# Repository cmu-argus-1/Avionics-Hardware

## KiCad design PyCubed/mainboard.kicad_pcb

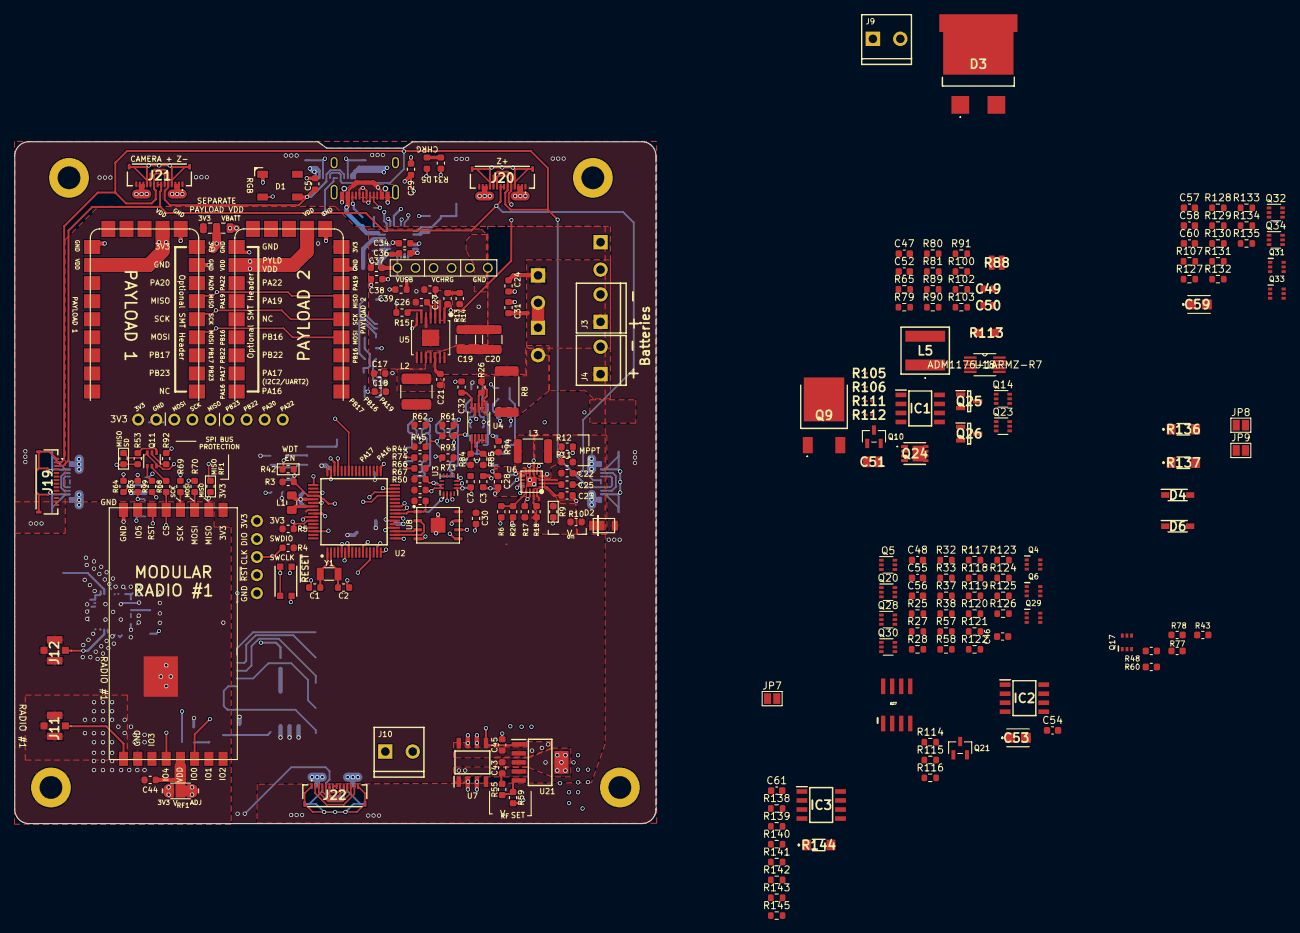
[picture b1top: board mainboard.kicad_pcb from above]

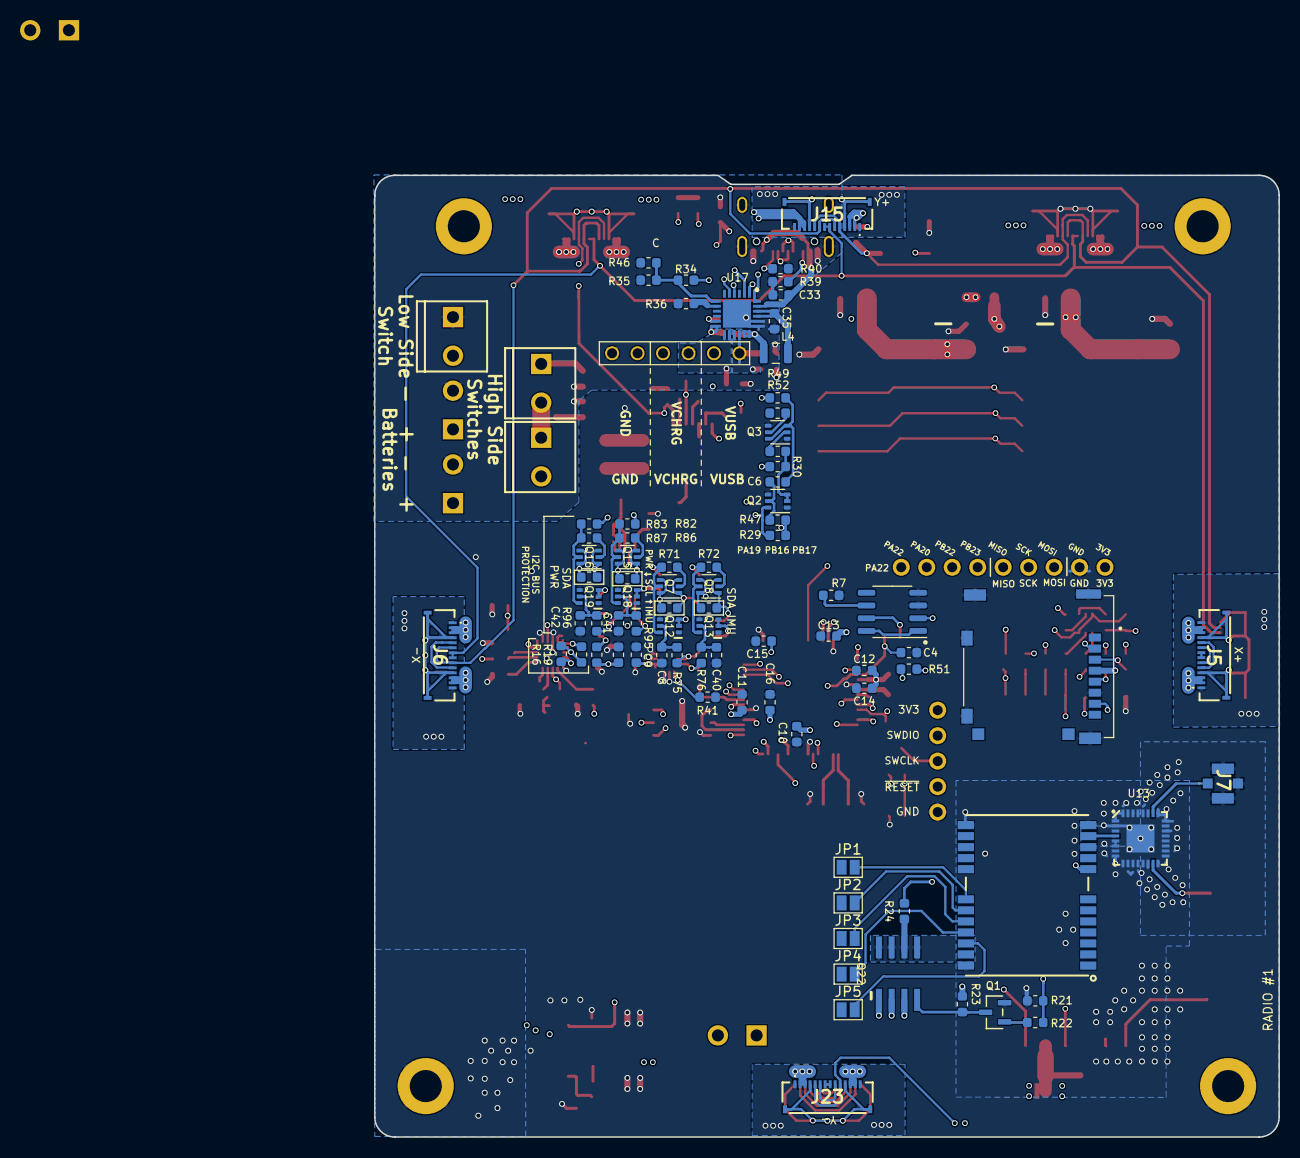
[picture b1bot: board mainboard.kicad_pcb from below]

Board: 4 copper layers, 90.2 x 95.9 mm, 308 parts (85 on the bottom side), 215 nets.

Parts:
C1, C2: 8pF; C_0603_1608Metric
C3, C5, C7, C9, C10, C11, C21, C24, C30, C45, C61: 0.1uF; C_0603_1608Metric
C4, C12, C13, C15, C27, C33, C54, C60: 1uF; C_0603_1608Metric
C6, C14, C16, C22, C35, C39, C43, C44, C52: 10uF; C_0603_1608Metric
C8, C40, C41, C42, C46, C48, C55, C56, C57, C58: 10nF; C_0603_1608Metric
C17, C18, C28, C31, C37, C38: 22uF; C_0603_1608Metric
C19, C20: 100uF; C_1210_3225Metric
C23: 2.2uF; C_0603_1608Metric
C25: 22nF; C_0603_1608Metric
C26, C32, C47: 3.3nF; C_0603_1608Metric
C29, C34: 4.7uF; C_0603_1608Metric
C36: 47nF; C_0603_1608Metric
C49, C50: 0.1u; CAPC1608X87N
C51: 100u; CAPC2012X150N
C53, C59: CPH3225A
D1: WS2812B; LED_WS2812B_PLCC4_5.0x5.0mm_P3.2mm
D2: DFLS130L; PWRDI-123
D3: RB225NS-40TL; RFN10NS3STL
D4, D6: MBR0540T1G; SOD3716X135N
D5: GREEN LED; LED_0603_1608Metric
H1, H2, H3, H4: MountingHole_Pad; MountingHole_3.2mm_M3_DIN965_Pad
IC1: MAX1771ESA+; SOIC127P600X175-8N
IC2: PCF8523T_1,118; SOIC127P600X175-8N
IC3: UA741IDT; SOIC127P600X175-8N
J1: 503182-1852; MOLEX_503182-1852
J2: Conn_01x05; PinHeader_1x05_P2.54mm_Vertical
J3, J4, J9, J10, J16, J17, J18: 1985807; SCREWTERMINAL-3.5MM-2_LOCK
J5, J6, J15, J19, J20, J21, J22, J23: F3311A7H121014E200
J7, J11, J12: 73412-0114; 73412-0110
J8: Conn_01x09; PinHeader_1x09_P2.54mm_Vertical
J13: USB_C_Receptacle_USB2.0; USB_C_Receptacle_XKB_U262-161N-4BVC11
J14: Conn_01x06; PinHeader_1x06_P2.54mm_Vertical
JP1, JP2, JP3, JP4, JP5, JP7, JP8, JP9: SolderJumper_2_Open; SolderJumper-2_P1.3mm_Open_Pad1.0x1.5mm
JP6: Jumper_3_Bridged12; SolderJumper-3_P1.3mm_Bridged12_RoundedPad1.0x1.5mm
L1: 10uH; L_0805_2012Metric_Pad1.15x1.40mm_HandSolder
L2: 3.3uH; L_2141
L3: 33uH; L_1812_4532Metric
L4: 1uH; L_2510
L5: 22u; PA5432223NLT
Q1, Q10, Q21: IRLML2803; SOT-23
Q2, Q3, Q5, Q7, Q8, Q14, Q15, Q16, Q20, Q23, Q28, Q30, Q32, Q34: MBT2222ADW1T1; SOT-363_SC-70-6
Q4, Q6, Q12, Q13, Q17, Q18, Q19, Q29, Q31, Q33: BSS138DWQ-7
Q9: IRFR320TRPBF-BE3; IRFR320TRPBFBE3
Q11: MMDT2907; SOT-363_SC-70-6
Q22, Q27: NDS8434
Q24: SQS141ELNW-T1_GE3; SQS850ENT1_GE3
Q25, Q26: 2SC4713KT146R; SOT95P280X130-3N
R1: 316K; R_0603_1608Metric
R2: 110K; R_0603_1608Metric
R3, R4, R21, R24, R28, R31, R32, R43, R44, R45, R46, R52, R55, R57, R61, R62, R66, R67, R77, R78, R79, R82, R83, R84, R85, R103, R114, R122, R123, R128, R129, R133, R134, R139, R140, R141, R143, R145: 10K; R_0603_1608Metric
R5, R7, R41, R42, R50, R51: 10k; R_0603_1608Metric
R6, R92: 4.7k; R_0603_1608Metric
R8: 0.1; R_2512_6332Metric
R9: 107K; R_0603_1608Metric
R10, R53, R97, R98, R99, R101, R104, R108, R109, R117, R118, R125, R126: 0; R_0603_1608Metric
R11: 787K; R_0603_1608Metric
R12: 121K; R_0603_1608Metric
R13, R29, R89: 73.2K; R_0603_1608Metric
R14: 22.1K; R_0603_1608Metric
R15, R25, R30, R37, R48, R49, R73, R74, R90, R93, R94, R102, R107, R120, R131, R138, R142: 100K; R_0603_1608Metric
R16: 845K; R_0603_1608Metric
R17, R18: 100k; R_0603_1608Metric
R19: 2.1M; R_0603_1608Metric
R20: 3.01K; R_0603_1608Metric
R22, R68, R80, R115: 4.7K; R_0603_1608Metric
R23, R59, R81, R116: 3.3K; R_0603_1608Metric
R26, R63, R64, R65, R69, R70: 1K; R_0603_1608Metric
R27, R38, R60, R71, R72, R86, R87, R121, R127, R132: 680; R_0603_1608Metric
R33, R47, R58, R75, R76, R95, R96, R100, R119, R124, R130, R135: 200K; R_0603_1608Metric
R34: 5.23K; R_0603_1608Metric
R35: 30.1K; R_0603_1608Metric
R36: 3.16K; R_0603_1608Metric
R39, R40: 5.1k; R_0603_1608Metric
R54, R56: 0; R_0805_2012Metric
R88: 20m; ERJB30508
R91, R110: 20K; R_0603_1608Metric
R105, R111: 1k; ERJ1GJJ2R4C
R106: 10k; ERJ1GJJ2R4C
R112: 0; ERJ1GJJ2R4C
R113: 82m; ERJ6_B_BW_R_LW_CW_D
R136, R137: ERA-8VEB1500V; ERA8KEB1004V
R144: ERA-8PEB6803V; ERA8P
SW1: KMR231NG LFS; BTN_KMR2_4.6X2.8
U1: MAX706RESA; SO-8_3.9x4.9mm_P1.27mm
U2: ATSAMD51J19A-AU; QFP50P1200X1200X120-64N
U3: BMX160
U4, U18: ADM1176-1ARMZ-R7
U5: TPS54226PWPRPWP14_2P31X2P46-L; PWP14_2P31X2P46-L
U6: LTC4121; QFN-16-PAD
U7: KF50BD-TR; SOIC127P600X175-8N
U8: MR25H40MDF; SON127P600X500X90-9N
U10, U12: XTB-40; XTB40_payload
U13: EP2W+; QFN32-5X5MM
U14: S1216V8; S1216_24PIN_PACKAGE
U17: BQ25883RGER; QFN50P400X400X100-25N-D
U21: TPS7A4501DCQT
U23: RFM98PW; RFM95PW
Y1: 32.768kHz; Crystal_SMD_3215-2Pin_3.2x1.5mm

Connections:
3.3V: C5.1, C9.2, C10.1, C11.1, C13.1, C15.1, C16.1, C17.2, C18.2, C30.1, D1.1 (VDD), D4.2 (A), D6.2 (A), IC2.8 (VDD), IC3.7 (VCC+), J1.4 (VDD), J2.1, J5.5, J5.10, J6.5, J6.10, J8.1, J15.5, J15.10, J20.5, J20.10, J21.5, J21.10, J23.5, J23.10, JP6.3 (B), L2.2, Q22.1 (Source), Q22.2 (Source), Q22.3 (Source), Q27.1 (Source), Q27.2 (Source), Q27.3 (Source), R3.1, R4.1, R5.1, R13.2, R17.2, R18.2, R23.1, R25.1, R28.1, R32.1, R37.1, R43.1, R44.1, R45.1, R48.1, R50.2, R51.2, R54.1, R57.1, R61.1, R62.1, R66.1, R67.1, R73.1, R74.1, R77.1, R78.1, R82.1, R83.1, R84.1, R85.1, R93.1, R94.1, R107.1, R116.1, R120.1, R122.1, R123.1, R128.1, R129.1, R131.1, R133.1, R134.1, R139.1, R145.2, U1.2 (VCC), U2.4 (PA03), U2.8 (VDDANA), U2.21 (VDDIO), U2.34 (VDDIO1), U2.48 (VDDIO2), U2.56 (VDDIO3), U3.5 (VDDIO), U5.1 (VO), U8.8 (VDD), U10.9, U12.9, U18.9 (A1), U23.9 (3.3V)
/Avionics/BATTERY: C3.1, R1.2, R2.2, U2.15 (PA06)
/Avionics/XTAL1: C1.1, U2.1 (PA00), Y1.1
/Avionics/XTAL2: C2.1, U2.2 (PA01), Y1.2
/Power1/3V3_EN: C49.2, IC1.2 (V+), Q14.6 (C1), Q26.3 (C), R89.2, R106.1
/Power/3V3_EN: Q2.6 (C1), R29.2, U5.7 (EN)
/Power/REGN: C34.1, R31.2, U17.11 (REGN)
/Power/VCHRG_IN: C22.1, D2.C, R10.2, R11.2, U6.P$3 (IN)
/Power/V_RF: C43.2, JP6.1 (A), R55.1, U7.1 (VOUT), U21.4 (OUT)
/RF and GPS/PYLD12_VDD: R54.2, R56.1, U10.11, U10.16, U12.11, U12.16
AIN5: C61.1, IC3.6 (OUTPUT), J8.6, J19.5, R144.2, U2.14 (PA05)
BAT_THERM: J22.2, J22.13, R141.2, R142.2
BURN_RELAY_A: J22.7, J22.8, U2.28 (PB15)
DAC0: J8.8, J19.4, U2.3 (PA02)
ENAB_BURN1: J22.6, J22.9, U2.60 (PB31)
ENAB_BURN2: J22.5, J22.10, U2.32 (PA15)
ENAB_BURN3: J22.4, J22.11, U2.39 (PB16)
ENAB_BURN4: J22.3, J22.12, U2.40 (PB17)
ENAB_GPS: R21.1, R22.1, U2.62 (PB01)
ENAB_IMU: R114.1, R115.1, U2.9 (PB06)
ENAB_JET: R105.1, R111.1
ENAB_RF: U2.13 (PA04), U7.5 (INHIBIT), U21.1 (~SHDN)
FLASH_CS: R50.1, U2.24 (PB11), U8.1 (~CS)
FLASH_IO2: U2.19 (PA10), U8.3 (~WP)
FLASH_IO3: U2.20 (PA11), U8.7 (~HOLD)
FLASH_MISO: U2.18 (PA09), U8.2 (SO)
FLASH_MOSI: U2.17 (PA08), U8.5 (SI)
FLASH_SCK: U2.23 (PB10), U8.6 (SCK)
GND: C1.2, C2.2, C3.2, C4.1, C5.2, C7.2, C8.2, C9.1, C10.2, C11.2, C12.1, C13.2, C14.2, C15.2, C16.2, C17.1, C18.1, C19.2, C20.2, C22.2, C23.2, C26.2, C27.2, C28.2, C30.2, C32.1, C40.2, C41.2, C42.2, C43.1, C44.1, C45.1, C46.2, C47.1, C48.2, C49.1, C50.1, C51.1, C53.2 (-), C54.1, C55.2, C56.2, C57.2, C58.2, C59.2 (-), C60.1, D1.3 (VSS), H1.1, H2.1, H3.1, H4.1, IC1.3 (FB), IC1.6 (AGND), IC1.7 (GND), IC2.4 (VSS), IC3.4 (VCC-), J1.6 (VSS), J1.P1 (SHIELD), J1.P2 (SHIELD), J1.P3 (SHIELD), J1.P4 (SHIELD), J1.P5 (SHIELD), J2.5, J5.4, J5.11, J5.MP1, J5.MP2, J6.4, J6.11, J6.MP1, J6.MP2, J7.2 (GND_1), J7.3 (GND_2), J7.4 (GND_3), J8.2, J9.2, J11.2 (GND_1), J11.3 (GND_2), J11.4 (GND_3), J12.2 (GND_1), J12.3 (GND_2), J12.4 (GND_3), J14.5, J15.4, J15.11, J15.MP1, J15.MP2, J18.2, J19.1, J19.MP1, J19.MP2, J20.4, J20.11, J20.MP1, J20.MP2, J21.4, J21.11, J21.MP1, J21.MP2, J22.1, J22.14, J22.MP1, J22.MP2, J23.4, J23.11, J23.MP1, J23.MP2, Q1.2 (S), Q2.1 (E1), Q2.4 (E2), Q3.1 (E1), Q3.4 (E2), Q4.1 (S2), Q4.4 (S1), Q6.1 (S2), Q6.4 (S1), Q10.2 (S), Q12.1 (S2), Q12.4 (S1), Q13.1 (S2), Q13.4 (S1), Q14.1 (E1), Q14.4 (E2), Q17.1 (S2), Q17.4 (S1), Q18.1 (S2), Q18.4 (S1), Q19.1 (S2), Q19.4 (S1), Q21.2 (S), Q23.1 (E1), Q23.4 (E2), Q25.1 (E), Q29.1 (S2), Q29.4 (S1), Q31.1 (S2), Q31.4 (S1), Q33.1 (S2), Q33.4 (S1), R2.1, R7.1, R9.2, R12.1, R14.1, R20.1, R21.2, R41.2, R59.2, R79.2, R88.1, R112.1, R114.2, R140.2, R143.2, SW1.B (S), SW1.B' (S1), U1.3 (GND), U1.4 (PFI), U2.7 (GND), U2.22 (GND1), U2.33 (GND2), U2.47 (GND3), U2.54 (GND4), U3.2 (GND_1), U3.3 (GND_2), U3.6 (GNDIO), U3.7 (GND_3), U4.4 (GND), U5.5 (GND), U5.8 (PGND1), U5.9 (PGND2), U5.15 (EPAD), U6.P$5 (GND), U6.P$7 (FREQ), U6.P$12 (NTC), U6.P$17 (GND), U7.2 (GND_1), U7.3 (GND_2), U7.6 (GND_3), U7.7 (GND_4), U8.4 (VSS), U8.9 (EP), U10.8, U10.10, U10.15, U12.8, U12.10, U12.15, U13.1 (GND), U13.2 (GND), U13.3 (GND), U13.5 (GND), U13.6 (GND), U13.7 (GND), U13.8 (GND), U13.9 (GND), U13.10 (GND), U13.11 (GND), U13.12 (GND), U13.13 (GND), U13.14 (GND), U13.16 (GND), U13.17 (GND), U13.18 (GND), U13.19 (GND), U13.20 (GND), U13.21 (GND), U13.22 (GND), U13.23 (GND), U13.24 (GND), U13.25 (GND), U13.27 (GND), U13.28 (GND), U13.29 (GND), U13.30 (GND), U13.31 (GND), U13.32 (GND), U13.EP (GND), U14.10 (GND@10), U14.12 (GND@12), U14.13 (GND@13), U14.24 (GND@24), U18.4 (GND), U21.3 (GND_1), U21.6 (GND_2), U23.2 (GND), U23.16 (GND), U23.17 (GND)
GNDREF: C24.2, C29.2, C31.2, C33.1, C34.2, C35.1, C37.1, C38.1, C39.1, J3.2, J4.2, J13.A1 (GND), J13.A12 (GND), J13.S1 (SHIELD), J14.6, J18.1, R35.1, R36.1, R39.1, R40.1, R46.1, U17.19 (GND_1), U17.20 (GND_2), U17.25 (EP)
GPS_PWR_IN: Q22.5 (Drain), Q22.6 (Drain), Q22.7 (Drain), Q22.8 (Drain), R24.2, U14.23 (VCC)
IMU_PWR_IN: C7.1, Q27.5 (Drain), Q27.6 (Drain), Q27.7 (Drain), Q27.8 (Drain), U3.8 (VDD), U3.12 (CSB)
JETSON_PWR: J8.9, J9.1, R65.1, R113.1, U18.2 (SENSE)
JETSON_PWR_SENSE: Q24.5 (D_1), Q24.6 (D_2), Q24.7 (D_3), Q24.8 (D_4), Q24.9 (D_5), Q24.10 (D_6), Q24.11 (D_7), R113.2, U18.1 (VCC)
JETSON_RX: J19.7, U2.37 (PA18)
JETSON_TX: J19.9, U2.35 (PA16)
JETSON_XCK: J19.8, U2.36 (PA17)
L1_PROG: R6.1, R20.2, U6.P$13 (PROG)
MISO: J8.5, Q11.3 (C2), Q11.6 (C1), R101.2, R104.2, U2.31 (PA14), U10.6, U12.6
MISO_RF1: R99.2, R101.1, U23.10 (MISO)
MISO_SD: J1.7 (DAT0), R53.2, R104.1
MOSI: J8.3, R64.2, R70.1, U2.29 (PA12), U10.4, U12.4
MOSI_RF1: R70.2, U23.11 (MOSI)
MOSI_SD: J1.3 (CMD), R64.1
unnamed: C59.1 (+), C60.2, JP5.1 (A)
unnamed: D1.4 (DIN), U2.42 (PA21)
unnamed: D3.3 (A_2), L5.2, Q9.2 (D)
unnamed: D3.4 (K_2), Q24.1 (S_1), Q24.2 (S_2), Q24.3 (S_3), R81.1
unnamed: D4.1 (K), R136.1
unnamed: D5.2 (A), R31.1
unnamed: D6.1 (K), R137.1
unnamed: IC1.8 (CS), Q9.3 (S), R88.2
unnamed: IC1.1 (EXT), Q9.1 (G)
unnamed: C50.2, IC1.5 (REF)
unnamed: IC1.4 (SHDN), Q25.3 (C), R106.2, R112.2
unnamed: C61.2, IC3.2 (INVERTING_INPUT), R142.1, R144.1
unnamed: IC3.3 (NON-INVERTING_INPUT), R138.1, R143.1
unnamed: J7.1 (SIGNAL), U13.26 (PORT2)
unnamed: J12.1 (SIGNAL), U13.15 (PORT1)
unnamed: C37.2, C38.2, J14.1, U17.15 (SYS_1), U17.16 (SYS_2)
unnamed: C39.2, J14.3, U17.13 (BAT_1), U17.14 (BAT_2)
unnamed: J16.2, J17.1
unnamed: JP1.2 (B), U14.18 (SDA/NC)
unnamed: JP2.2 (B), U14.19 (SCL/NC)
unnamed: JP3.2 (B), U14.20 (TXD)
unnamed: JP4.2 (B), U14.21 (RXD)
unnamed: JP5.2 (B), R137.2, U14.22 (V_BCKP)
unnamed: JP7.2 (B), R136.2
unnamed: J19.11, JP8.2 (B)
unnamed: J19.10, JP9.2 (B)
unnamed: Q1.3 (D), Q22.4 (Gate), R23.2
unnamed: Q1.1 (G), R22.2
unnamed: Q2.2 (B1), Q2.3 (C2), R30.2, R110.2
unnamed: C6.2, Q2.5 (B2), R47.2
unnamed: Q3.2 (B1), R110.1
unnamed: C6.1, Q3.3 (C2), Q3.6 (C1), R49.2
unnamed: Q3.5 (B2), R52.1
unnamed: Q4.6 (D1), Q5.5 (B2), R27.2, R28.2
unnamed: Q4.2 (G2), Q4.3 (D2), R25.2
unnamed: C46.1, Q4.5 (G1), R33.2
unnamed: Q5.2 (B1), R27.1
unnamed: Q6.2 (G2), Q6.3 (D2), R37.2
unnamed: C48.1, Q6.5 (G1), R58.2
unnamed: Q7.2 (B1), R71.1
unnamed: Q8.2 (B1), R72.1
unnamed: Q10.3 (D), Q24.4 (G), R81.2
unnamed: Q10.1 (G), R80.2
unnamed: Q11.2 (B1), R68.1
unnamed: Q11.1 (E1), R99.1
unnamed: Q11.5 (B2), R92.1
unnamed: Q11.4 (E2), R53.1
unnamed: Q7.5 (B2), Q12.6 (D1), R61.2, R71.2
unnamed: Q12.2 (G2), Q12.3 (D2), R73.2
unnamed: C8.1, Q12.5 (G1), R75.2
unnamed: Q8.5 (B2), Q13.6 (D1), R62.2, R72.2
unnamed: Q13.2 (G2), Q13.3 (D2), R74.2
unnamed: C40.1, Q13.5 (G1), R76.2
unnamed: Q14.2 (B1), Q14.3 (C2), R90.2, R91.2
unnamed: C52.2, Q14.5 (B2), R100.2
unnamed: Q15.2 (B1), R86.1
unnamed: Q15.5 (B2), Q18.6 (D1), R82.2, R86.2
unnamed: Q16.2 (B1), R87.1
unnamed: Q16.5 (B2), Q19.6 (D1), R83.2, R87.2
unnamed: Q17.6 (D1), Q28.5 (B2), R60.2, R77.2
unnamed: Q17.2 (G2), Q17.3 (D2), R48.2
unnamed: C55.1, Q17.5 (G1), R119.2
unnamed: Q18.2 (G2), Q18.3 (D2), R93.2
unnamed: C41.1, Q18.5 (G1), R95.2
unnamed: Q19.2 (G2), Q19.3 (D2), R94.2
unnamed: C42.1, Q19.5 (G1), R96.2
unnamed: Q20.2 (B1), R38.1
unnamed: Q6.6 (D1), Q20.5 (B2), R38.2, R43.2
unnamed: Q21.3 (D), Q27.4 (Gate), R116.2
unnamed: Q21.1 (G), R115.2
unnamed: Q23.2 (B1), R91.1
unnamed: C52.1, Q23.3 (C2), Q23.6 (C1), R102.2
unnamed: Q23.5 (B2), R103.1
unnamed: Q25.2 (B), R105.2
unnamed: Q26.2 (B), R111.2
unnamed: C51.2, Q26.1 (E), R79.1, R80.1
unnamed: Q28.2 (B1), R60.1
unnamed: Q29.6 (D1), Q30.5 (B2), R121.2, R122.2
unnamed: Q29.2 (G2), Q29.3 (D2), R120.2
unnamed: C56.1, Q29.5 (G1), R124.2
unnamed: Q30.2 (B1), R121.1
unnamed: Q31.6 (D1), Q32.5 (B2), R127.2, R128.2
unnamed: Q31.2 (G2), Q31.3 (D2), R107.2
unnamed: C57.1, Q31.5 (G1), R130.2
unnamed: Q32.2 (B1), R127.1
unnamed: Q33.6 (D1), Q34.5 (B2), R132.2, R133.2
unnamed: Q33.2 (G2), Q33.3 (D2), R131.2
unnamed: C58.1, Q33.5 (G1), R135.2
unnamed: Q34.2 (B1), R132.1
unnamed: R138.2, R139.2, R140.1
unnamed: R141.1, R145.1
unnamed: U1.1 (~MR), U1.8 (~WDO)
unnamed: R42.2, U1.7 (~RESET)
unnamed: R6.2, U2.16 (PA07)
unnamed: C12.2, C14.1, L1.1, U2.53 (VDDCORE)
unnamed: L1.2, U2.55 (VSW)
unnamed: R41.1, U3.1 (SDO)
unnamed: R26.2, U4.3 (ON)
unnamed: C32.2, U4.5 (TIMER)
unnamed: R15.1, U5.6 (PG)
unnamed: C26.1, U5.4 (SS)
unnamed: C21.1, L2.1, U5.10 (SW1), U5.11 (SW2)
unnamed: C21.2, U5.12 (VBST)
unnamed: R13.1, R14.2, U5.2 (VFB)
unnamed: C27.1, R15.2, U5.3 (VREG5)
unnamed: C25.1, U6.P$2 (BOOST)
unnamed: L3.1, U6.P$8 (CHGSNS)
unnamed: R16.2, R19.2, U6.P$10 (FB)
unnamed: R16.1, U6.P$11 (FBG)
unnamed: C23.1, U6.P$1 (INTVCC)
unnamed: R11.1, R12.2, U6.P$6 (MPPT)
unnamed: R9.1, R10.1, U6.P$16 (RUN)
unnamed: C25.2, L3.2, U6.P$4 (SW)
unnamed: R18.1, U6.P$15 (~FAULT)
unnamed: U13.4 (SUM_PORT), U14.11 (RF_IN)
unnamed: R24.1, U14.8 (RSTN)
unnamed: C36.2, U17.12 (BTST)
unnamed: R36.2, U17.8 (ILIM)
unnamed: C35.2, L4.1, U17.21 (PMID_1), U17.22 (PMID_2)
unnamed: C36.1, L4.2, U17.17 (SW_1), U17.18 (SW_2)
unnamed: R65.2, U18.3 (ON)
unnamed: C47.2, U18.5 (TIMER)
unnamed: R55.2, R59.1, U21.5 (SENSE/ADJ)
PB07: J19.12, U2.10 (PB07)
PB09: J19.13, U2.12 (PB09)
PB14: J19.14, U2.27 (PB14)
PB22: J8.7, J19.6, U2.49 (PB22)
RF1_ANT: J11.1 (SIGNAL), U23.1 (ANT)
RF1_CS: R5.2, R68.2, U2.59 (PB30), U23.13 (NSS)
RF1_IO0: U2.6 (PB05), U23.6 (GPIO_0)
RF1_IO4: U2.5 (PB04), U23.4 (GPIO_4)
RF1_RST: U2.61 (PB00), U23.14 (RESET)
RX: JP3.1 (A), JP8.1 (A), U2.64 (PB03)
SCK: J8.4, R63.2, R69.2, U2.30 (PA13), U10.5, U12.5
SCK_RF1: R69.1, U23.12 (SCK)
SCK_SD: J1.5 (CLK), R63.1
SCL: Q5.1 (E1), Q5.3 (C2), Q7.1 (E1), Q7.3 (C2), Q15.1 (E1), Q15.3 (C2), Q28.1 (E1), Q28.3 (C2), Q32.1 (E1), Q32.3 (C2), R45.2, R97.2, R108.2, R117.2, R125.2, U2.26 (PB13)
SCL2: J5.6, J5.9, J6.6, J6.9, J15.6, J15.9, J19.2, J20.6, J20.9, J21.6, J21.9, J23.6, J23.9, U2.44 (PA23)
SCL_GPS: JP2.1 (A), Q32.4 (E2), Q32.6 (C1), R129.2, R130.1
SCL_IMU: Q7.4 (E2), Q7.6 (C1), R66.2, R75.1, R97.1, U3.13 (SCX)
SCL_JETSON_PWR: Q28.4 (E2), Q28.6 (C1), R78.2, R119.1, R125.1, U18.6 (SCL)
SCL_PWR: Q15.4 (E2), Q15.6 (C1), R84.2, R95.1, R108.1, U4.6 (SCL), U17.5 (SCL)
SCL_RTC: IC2.6 (SCL), Q5.4 (E2), Q5.6 (C1), R32.2, R33.1, R117.1
SDA: Q8.1 (E1), Q8.3 (C2), Q16.1 (E1), Q16.3 (C2), Q20.1 (E1), Q20.3 (C2), Q30.1 (E1), Q30.3 (C2), Q34.1 (E1), Q34.3 (C2), R44.2, R98.2, R109.2, R118.2, R126.2, U2.25 (PB12)
SDA2: J5.7, J5.8, J6.7, J6.8, J15.7, J15.8, J19.3, J20.7, J20.8, J21.7, J21.8, J23.7, J23.8, U2.43 (PA22)
SDA_GPS: JP1.1 (A), Q34.4 (E2), Q34.6 (C1), R134.2, R135.1
SDA_IMU: Q8.4 (E2), Q8.6 (C1), R67.2, R76.1, R98.1, U3.14 (SDX)
SDA_JETSON_PWR: Q30.4 (E2), Q30.6 (C1), R123.2, R124.1, R126.1, U18.7 (SDA)
SDA_PWR: Q16.4 (E2), Q16.6 (C1), R85.2, R96.1, R109.1, U4.7 (SDA), U17.4 (SDA)
SDA_RTC: IC2.5 (SDA), Q20.4 (E2), Q20.6 (C1), R57.2, R58.1, R118.1
SD_CS: J1.2 (CD/DAT3), R51.1, R92.2, U2.51 (PA27)
STAT: D5.1 (K), U17.2 (STAT)
SWCLK: J2.3, R4.2, U2.57 (PA30)
SWDIO: J2.2, U2.58 (PA31)
THM: R34.2, R35.2, R46.2, U17.7 (TS)
TX: JP4.1 (A), JP9.1 (A), U2.63 (PB02)
USB_CC1: J13.A5 (CC1), R40.2
USB_CC2: J13.B5 (CC2), R39.2
USB_D+: J13.A6 (D+), J13.B6 (D+), U2.46 (PA25), U17.24 (D+)
USB_D-: J13.A7 (D-), J13.B7 (D-), U2.45 (PA24), U17.1 (D-)
VBATT: C19.1, C20.1, C28.1, C45.2, J5.2, J5.3, J5.12, J5.13, J6.2, J6.3, J6.12, J6.13, J10.1, J10.2, J14.2, J15.2, J15.3, J15.12, J15.13, J20.2, J20.3, J20.12, J20.13, J21.2, J21.3, J21.12, J21.13, J23.2, J23.3, J23.12, J23.13, L5.1, R1.1, R8.1, R19.1, R26.1, R29.1, R30.1, R47.1, R49.1, R56.2, R89.1, R90.1, R100.1, R102.1, U4.2 (SENSE), U5.13 (VIN), U5.14 (VCC), U6.P$9 (BAT), U7.8 (VIN), U21.2 (IN)
VBATT_SENSE: J17.2, R8.2, U4.1 (VCC)
VBUS_IN: C29.1, C33.2, J13.A4 (VBUS), J13.A9 (VBUS), R34.1, U17.23 (VBUS)
VBUS_RESET: R52.2, R103.2, U2.41 (PA20)
VCC_RF1: C44.2, JP6.2 (C), U23.5 (VCC)
VCELL: C53.1 (+), C54.2, IC2.3 (VBAT), JP7.1 (A)
VCHRG: C24.1, C31.1, J3.1, J4.1, J14.4, J16.1
VSOLAR: D2.A, J5.1, J5.14, J6.1, J6.14, J15.1, J15.14, J20.1, J20.14, J21.1, J21.14, J23.1, J23.14
WDT_WDI: R7.2, U1.6 (~WDI), U2.50 (PB23)
~CHRG: R17.1, U2.11 (PB08), U6.P$14 (~CHRG)
~RESET: C4.2, J2.4, R3.2, R42.1, SW1.A, SW1.A' (P1), U2.52 (RESETN)

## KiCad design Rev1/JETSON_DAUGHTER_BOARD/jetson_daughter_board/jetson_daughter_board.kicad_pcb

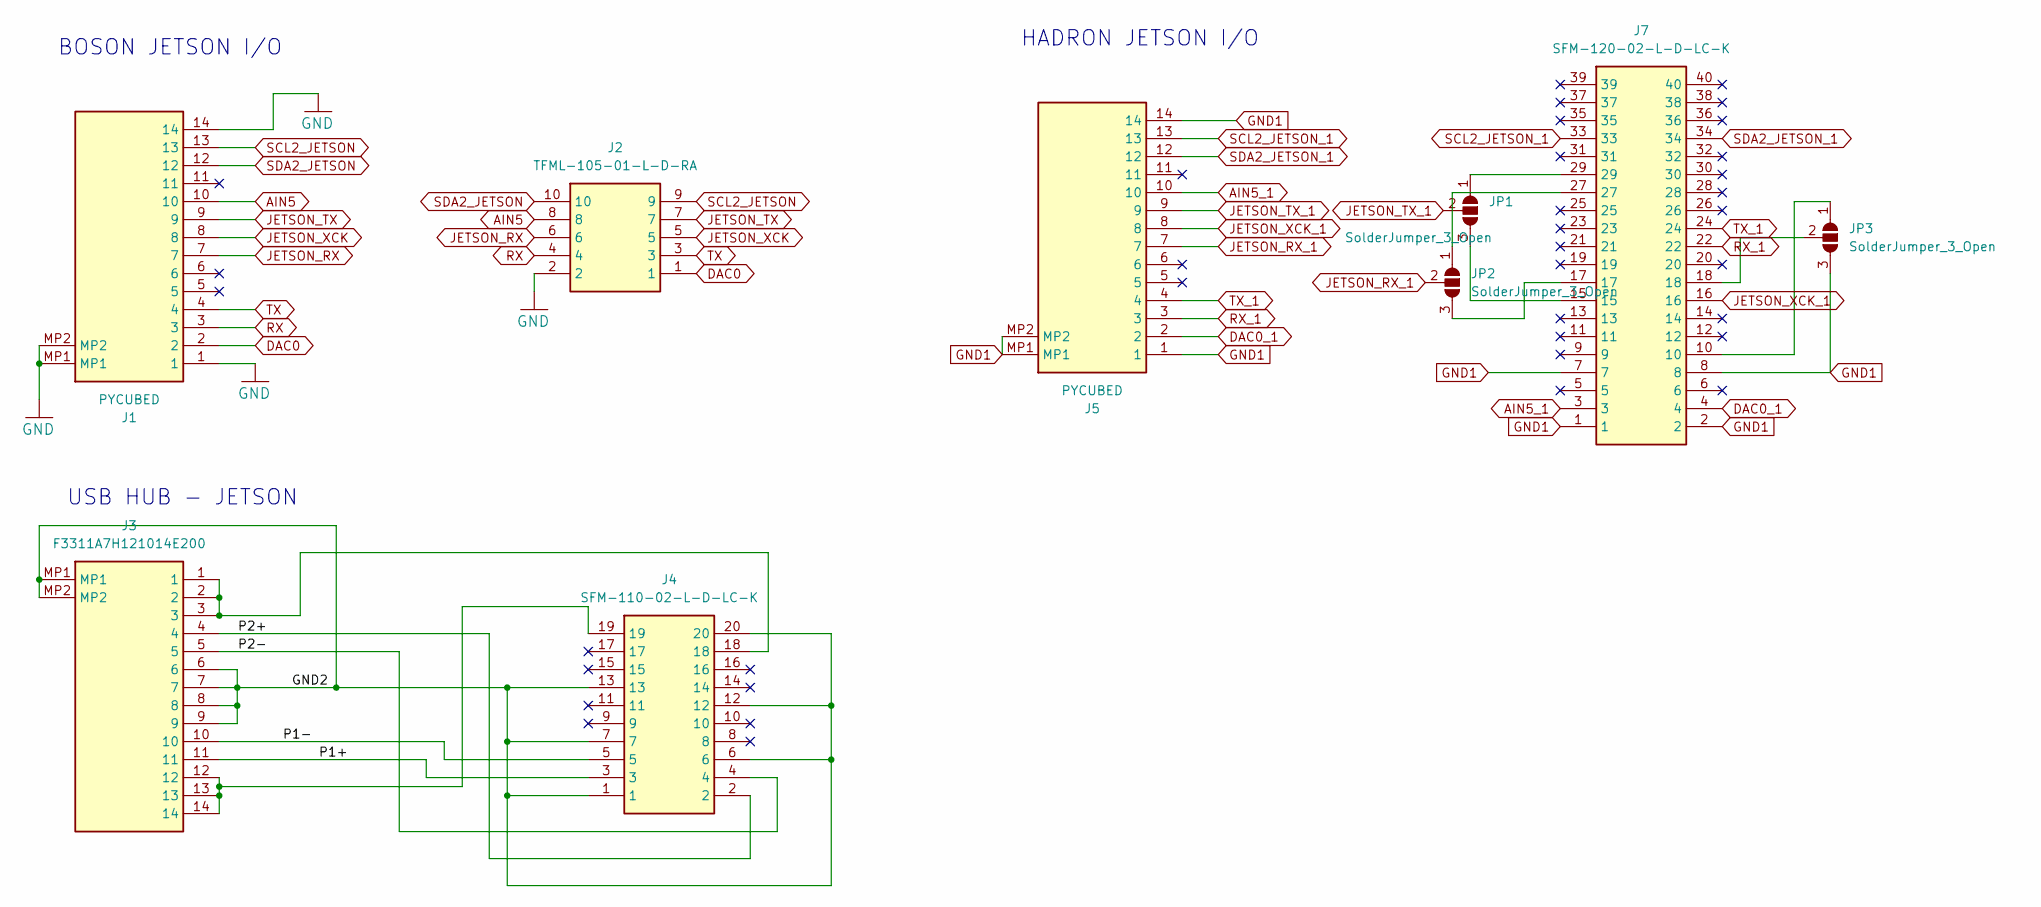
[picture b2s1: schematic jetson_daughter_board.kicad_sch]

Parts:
J1, J5: PYCUBED; F3311A7H121014E200; Manufacturer_Part_Number F3311A7H121014E200
J2: TFML-105-01-L-D-RA; TFML10501LDRA; Manufacturer_Part_Number TFML-105-01-L-D-RA; Mouser Part Number 200-TFML10501LDRA
J3: F3311A7H121014E200; Manufacturer_Part_Number F3311A7H121014E200
J4: SFM-110-02-L-D-LC-K; SFM11002LDLCK; Manufacturer_Part_Number SFM-110-02-L-D-LC-K; Mouser Part Number 200-SFM11002LDLCK
J7: SFM-120-02-L-D-LC-K; SFM12002LDLCK; Manufacturer_Part_Number SFM-120-02-L-D-LC-K; Mouser Part Number 200-SFM12002LDLCK
JP1, JP2, JP3: SolderJumper_3_Open; SolderJumper-3_P1.3mm_Open_Pad1.0x1.5mm

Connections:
/P1+: J3.11, J4.3
/P1-: J3.10, J4.5
/P2+: J3.4, J4.2
/P2-: J3.5, J4.4
AIN5: J1.10, J2.8
AIN5_1: J5.10, J7.3
DAC0: J1.2, J2.1
DAC0_1: J5.2, J7.4
GND: J1.1, J1.14, J1.MP1, J1.MP2, J2.2
GND1: J5.1, J5.14, J5.MP1, J5.MP2, J7.1, J7.2, J7.7, J7.8, JP3.3 (B)
GND2: J3.6, J3.7, J3.8, J3.9, J3.MP1, J3.MP2, J4.1, J4.6, J4.7, J4.12, J4.13, J4.20
JETSON_RX: J1.7, J2.6
JETSON_RX_1: J5.7, JP2.2 (C)
JETSON_TX: J1.9, J2.7
JETSON_TX_1: J5.9, JP1.2 (C)
JETSON_XCK: J1.8, J2.5
JETSON_XCK_1: J5.8, J7.16
unnamed: J3.1, J3.2, J3.3, J4.18
unnamed: J3.12, J3.13, J3.14, J4.19
unnamed: J7.29, JP1.1 (A)
unnamed: J7.15, JP1.3 (B)
unnamed: J7.27, JP2.1 (A)
unnamed: J7.17, JP2.3 (B)
unnamed: J7.10, JP3.1 (A)
unnamed: J7.18, JP3.2 (C)
RX: J1.3, J2.4
RX_1: J5.3, J7.22
SCL2_JETSON: J1.13, J2.9
SCL2_JETSON_1: J5.13, J7.33
SDA2_JETSON: J1.12, J2.10
SDA2_JETSON_1: J5.12, J7.34
TX: J1.4, J2.3
TX_1: J5.4, J7.24

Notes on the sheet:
USB HUB - JETSON
BOSON JETSON I/O
HADRON JETSON I/O

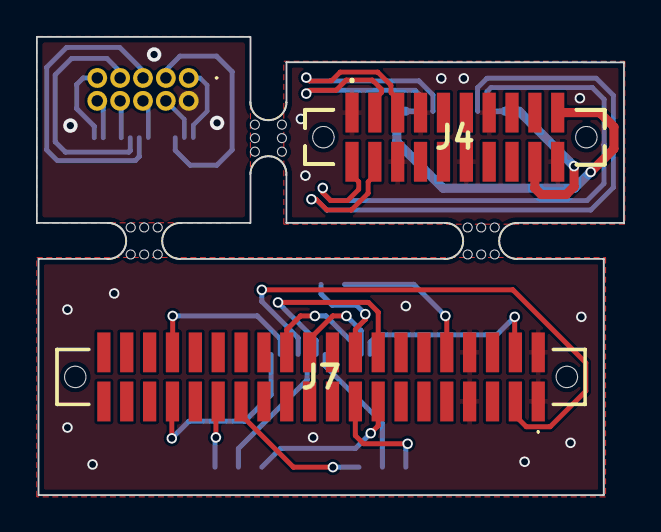
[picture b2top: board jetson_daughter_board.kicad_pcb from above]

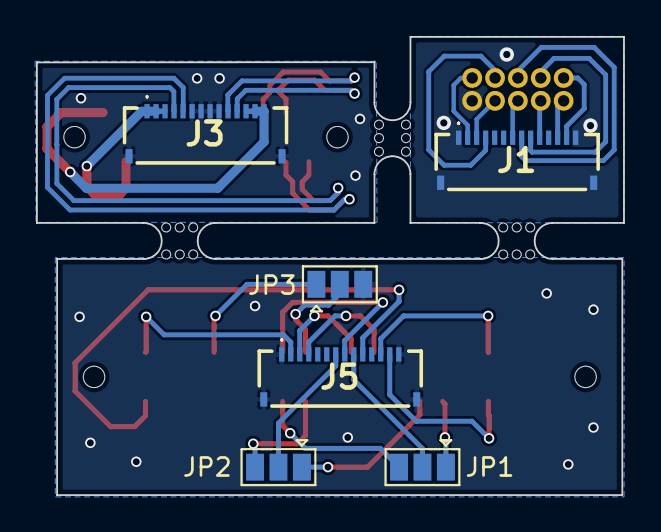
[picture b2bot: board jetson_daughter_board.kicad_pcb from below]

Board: 2 copper layers, 32.6 x 25.5 mm, 12 parts (6 on the bottom side), 33 nets.

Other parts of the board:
mouse-bite-2mm-slot, mouse-bite-2mm-slot#2, mouse-bite-2mm-slot#3: VAL**; mouse-bite-2mm-slot

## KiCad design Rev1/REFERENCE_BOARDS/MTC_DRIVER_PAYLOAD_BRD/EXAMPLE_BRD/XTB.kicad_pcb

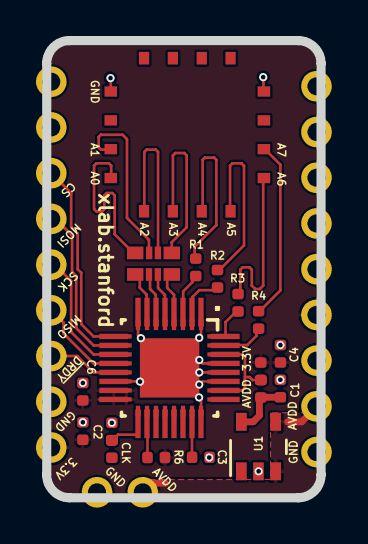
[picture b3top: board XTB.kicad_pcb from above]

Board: 2 copper layers, 15.2 x 25.4 mm, 23 parts (0 on the bottom side), 34 nets.

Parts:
C1, C3: 1uF; C_0402_1005Metric
C2, C6: 0.1uF; C_0402_1005Metric
C4: 0.33uF; C_0402_1005Metric
J1, J2: Conn_01x09; PinHeader_1x09_P2.54mm_Vertical
J3, J4: Conn_01x01; PinHeader_CUSTOM2
R1, R2, R3, R4: 47; R_0402_1005Metric
R5, R7, R8, R9: 0; R_0402_1005Metric
R6: 10K; R_0402_1005Metric
RA2: EXB-28VR000X; C_ARRAY_EXB28V
U1: LM4120-1P8DBV; LM4120IM5X-1.8&slash_NOPB
U2: M-QFN28_B; HVQFN_C
U4: Value; ADS124S08_QFP
U5: Value; ADS124208_withpad

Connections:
/3.3V: C2.1, C4.2, C6.1, J1.9, J2.6, R6.1, R8.2, U4.15, U4.16, U5.15, U5.16
/ADC_~RST: R6.2, U4.18, U5.18
/AIN0: RA2.1, U4.7, U5.7
/AIN1: RA2.2, U4.6, U5.6
/AIN1_QFN: RA2.7, U2.15
/AIN2: RA2.3, U4.5, U5.5
/AIN2_QFN: RA2.6, U2.1
/AIN3: RA2.4, U4.4, U5.4
/AIN3_QFN: RA2.5, U2.2
/AIN4: R1.1, U4.3, U5.3
/AIN4_QFN: R1.2, U2.3
/AIN5: R2.1, U4.2, U5.2
/AIN5_QFN: R2.2, U2.4
/AIN6: R3.1, U4.32, U5.32
/AIN7: R4.1, U4.31, U5.31
/AIN8: U4.22, U5.22
/AIN9: U4.21, U5.21
/AIN10: U4.20, U5.20
/AIN11: U4.19, U5.19
/AVDD: R8.1, R9.2, U4.26, U4.30, U5.26, U5.30
/CLK: R5.1, R7.2, U4.17, U5.17
/GND: C1.2, C2.2, C3.2, C4.1, C6.2, J1.1, J1.8, J2.5, J2.9, J4.1, R7.1, U1.2, U2.8, U2.13, U4.1, U4.8, U4.14, U4.24, U4.27, U4.28, U4.29, U5.1, U5.8, U5.14, U5.24, U5.27, U5.28, U5.29, U5.33
/SPI_CS: J1.3, U4.9, U5.9
/SPI_MISO: J1.6, U4.12, U5.12
/SPI_MOSI: J1.4, U4.10, U5.10
/SPI_SCK: J1.5, U4.11, U5.11
/~DRDY: J1.7, U4.13, U5.13
AIN0_QFN: RA2.8, U2.16
AIN6_QFN: R3.2, U2.5
AIN7_QFN: R4.2, U2.6
AVDD_IN: J2.8, J3.1, U1.3, U1.4
AVDD_OUT: C1.1, R9.1, U1.5
unnamed: C3.1, U4.23, U5.23
unnamed: U4.25, U5.25

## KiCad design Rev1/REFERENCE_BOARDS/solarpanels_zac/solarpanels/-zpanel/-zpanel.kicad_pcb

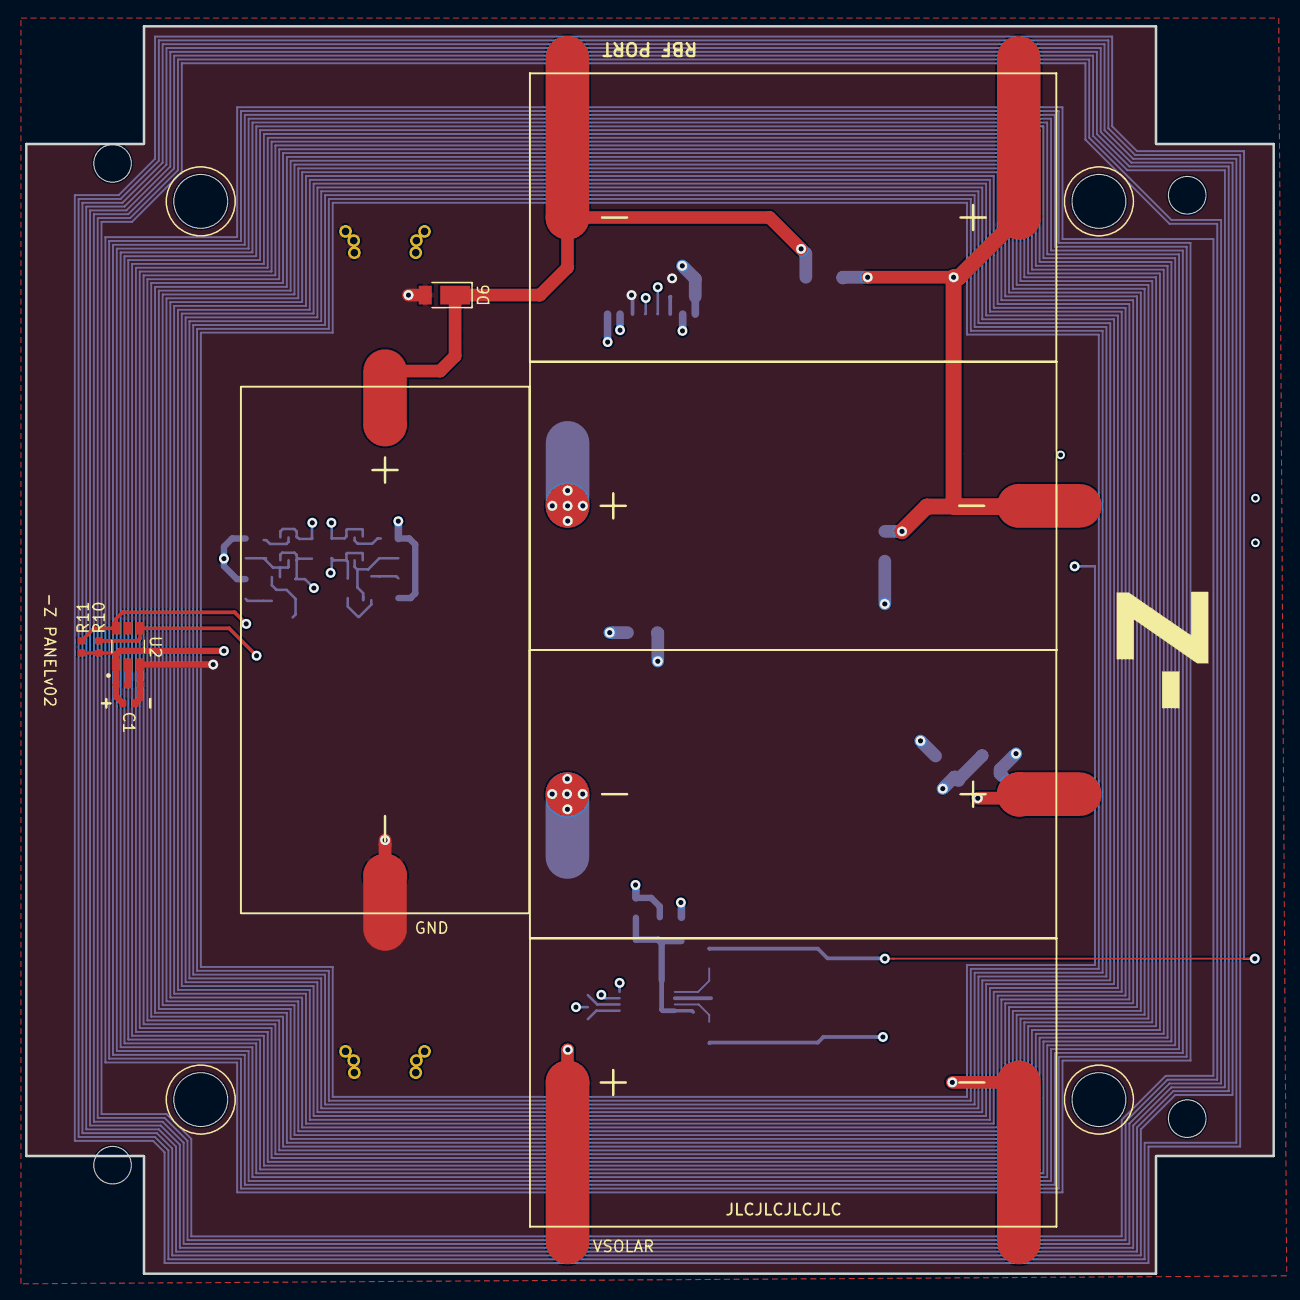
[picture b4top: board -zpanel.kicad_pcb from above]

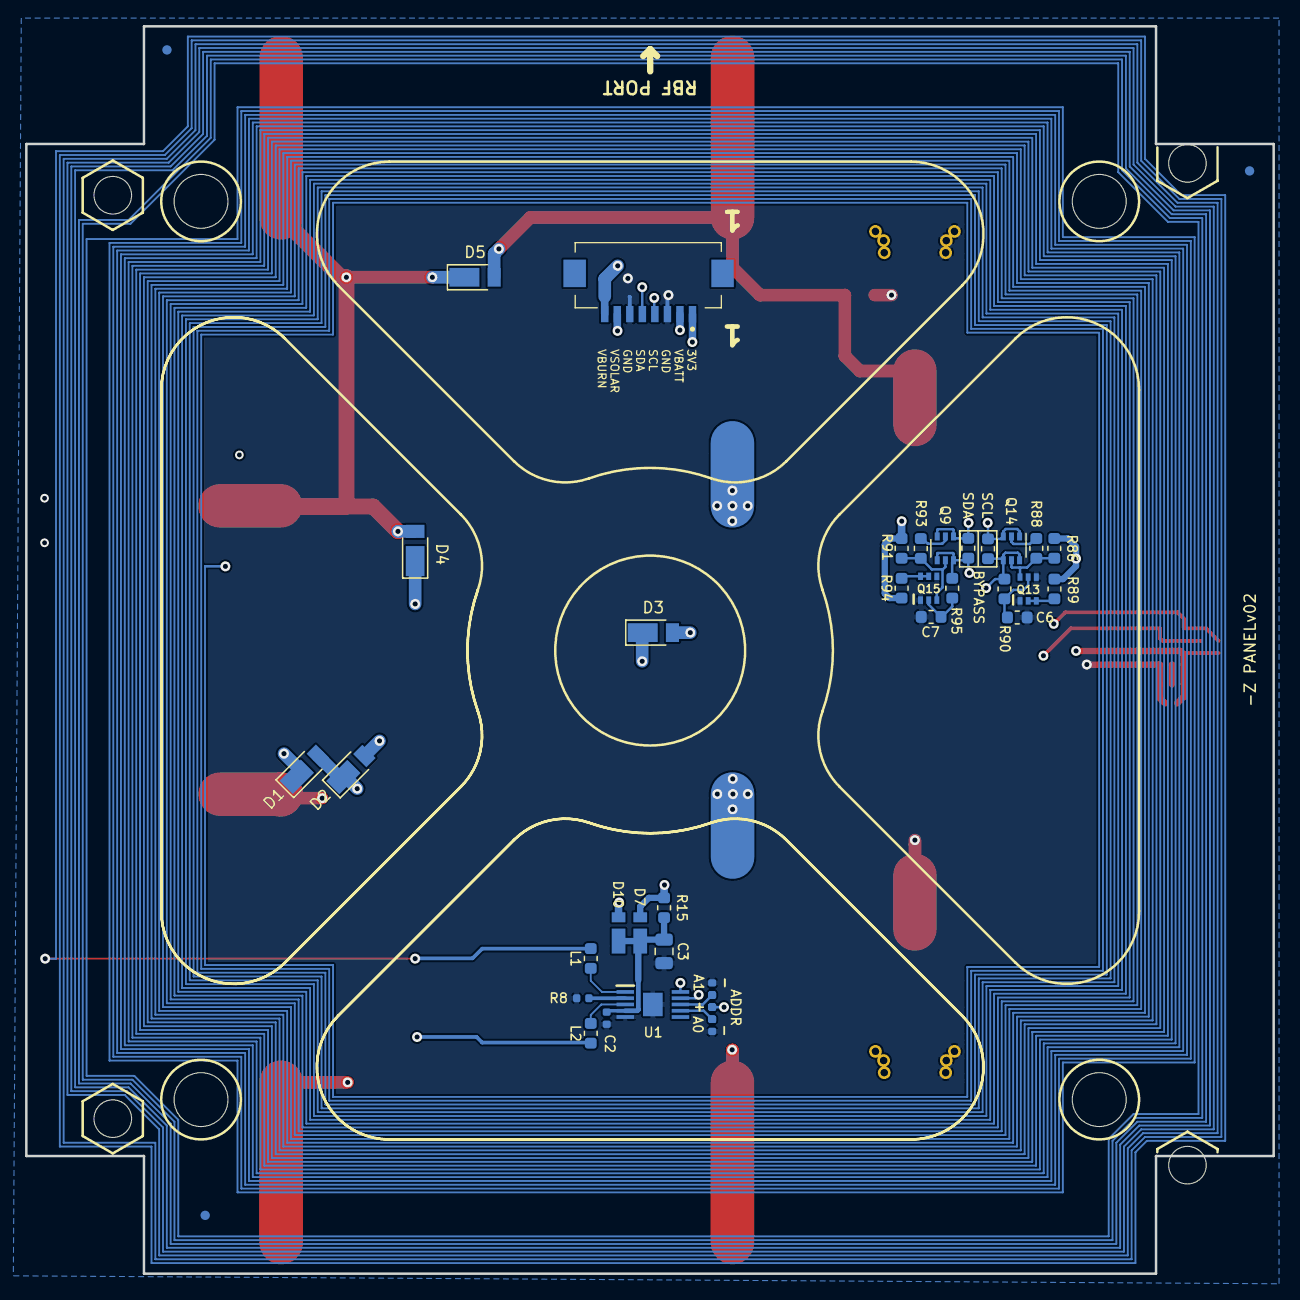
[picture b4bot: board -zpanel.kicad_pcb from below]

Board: 6 copper layers, 99.5 x 99.5 mm, 62 parts (38 on the bottom side), 31 nets.

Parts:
@HOLE0, @HOLE1, @HOLE2, @HOLE3: (no value)
C1, C2: 0.1uF; C_0402_1005Metric
C3: 10uF; C_0805_2012Metric
C6, C7: 10nF; C_0603_1608Metric
D1, D2, D3, D4, D5, D6: SBD; D_PowerDI-123
D7, D10: SBD; SOD-323HE
F1, F2: BURN_TERM; BURN_WIRE
FID1, FID2, FID3: Fiducial; Fiducial_0.75mm_Mask1.5mm
H1, H2, H3, H4: MountingHole; MountingHole_4.3mm_M4
J2: XF3M(1)-0815-1B; XF3M108151B
L1, L2: TBD; L_0603_1608Metric
Q9, Q14: MBT2222ADW1T1; SOT-363_SC-70-6
Q13, Q15: BSS138DWQ-7
R1, R2, R4, R5, R6, R7, R8: 0; R_0402_1005Metric
R10, R11: 10K; R_0402_1005Metric
R15, R79, R80: 0; R_0603_1608Metric
R86, R89, R91, R94: 10K; R_0603_1608Metric
R88, R93: 600; R_0603_1608Metric
R90, R95: 100K; R_0603_1608Metric
Ref**: Val**; holliday
Ref**#2: Val**; -zpanel
SC1, SC2, SC3, SC4, SC5: Solar_Cell; SM141K06L
U1: DRV8830DGQR
U2: TSL2561

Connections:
+3V3: C1.1, D7.2, J2.1, R1.2, R4.2, R5.2, R10.2, R11.2, R15.1, R86.1, R89.2, R91.1, R94.2, U2.1
/VBURN: F1.1, F2.1, J2.8
/VSOLAR: D1.1, J2.7
/torque-coil: L1.1, L2.1
GND: C1.2, C2.2, C3.2, C6.2, C7.2, D6.2, F1.2, F2.2, J2.3, J2.6, Q13.1, Q13.4, Q15.1, Q15.4, R2.1, R6.1, R7.1, R8.1, SC5.2, U1.5, U1.11, U2.3
unnamed: C2.1, C3.1, D7.1, D10.1, R15.2, U1.4
unnamed: C6.1, Q13.5, R90.1
unnamed: C7.1, Q15.2, R95.1
unnamed: D1.2, D2.1, SC1.1
unnamed: D2.2, D3.1, SC1.2, SC2.1
unnamed: D3.2, D4.1, SC2.2, SC3.1
unnamed: D4.2, D5.1, SC3.2, SC4.1
unnamed: D5.2, D6.1, SC4.2, SC5.1
unnamed: J2.MP1, J2.MP2
unnamed: L1.2, U1.1
unnamed: L2.2, U1.3
unnamed: Q9.2, R93.1
unnamed: Q13.2, Q13.3, R89.1
unnamed: Q13.6, Q14.5, R86.2, R88.1
unnamed: Q14.2, R88.2
unnamed: Q9.5, Q15.3, R91.2, R93.2
unnamed: Q15.5, Q15.6, R94.1
unnamed: R1.1, R2.2, U2.2
unnamed: R4.1, R6.2, U1.8
unnamed: R5.1, R7.2, U1.7
unnamed: R8.2, U1.2
SCL: Q14.4, Q14.6, R10.1, R79.2, R90.2, U1.10, U2.4
SCL1_b4iso: J2.4, Q14.1, Q14.3, R79.1
SDA: Q9.4, Q9.6, R11.1, R80.2, R95.2, U1.9, U2.6
SDA1_b4iso: J2.5, Q9.1, Q9.3, R80.1
VBATT: D10.2, J2.2

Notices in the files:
parts and their libraries:
Copyright 2016 Accelerated Designs. All rights reserved.
